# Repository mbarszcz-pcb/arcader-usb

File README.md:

# ArcadeR-USB
A Replacement PCB that brings USB connectivity to the Retroradionics ArcadeR Joystick based on the Daemonbite Arcade Encoder and the Arduino Leonardo.

Quick Links
* [Schematic](pdf/arcader-usb-1.0-schematic.pdf)
* [Gerber Files](gerbers)
* [PCB Renderings](images/pcb)
* [Photos](images/photos)

## Introduction
The ArcadeR USB is an open source PCB project with firmware based on the open source [DaemonBite Arcade Encoder Firmware](https://github.com/MickGyver/DaemonBite-Arcade-Encoder) and circuit design based on the Arduino Leonardo.  The original PCB inside the ArcadeR output provided Atari/Amiga/C64 style outputs through a DB9 connector.  While the DB9 connector is great for retro computers and consoles, using the ArcadeR with a PC, Raspberry Pi, or MiSTER requires external adapters.  Moreover, many of the inexpensive adapters introduced significant input latency, running the experience.

The ArcadeR USB aims to solve these problems plus introduces some extra features by simply providing a new PCB that fits inside the joystick with no modifications require and allows you to simply plug in the internal joystick and button cables.

## Features:
* DIY / Open Source
* Simple installation. Remove the screws, replace the PCB and cable, and plug everything back in
* Built around the Atmega32U4, Arduino Libraries, and DaemonBite Arcade Encoder firmware.  Use the firmware as-is or customize however you see fit
* Functions as a standard HID Gamepad, so no extra drivers required
* Replaces the two front latching switches with tactile switches wired as individually addressable buttons.  Now the front buttons can be used for Start/Select, Coin/Start, pressed together to bring up menus in emulation, or even used as an additional button in games
* Quickly link/unlink the two buttons on the fly with a simple button press.  Unlike with the original PCB, no opening of the case and rewiring of the buttons is required to link the two main buttons.  Simply press and hold the top two buttons for 1 second to link or unlink the buttons.  Now you can quickly switch between left and right handed use for 1 button games, or unlink the buttons and use them independently with arcade games that take advantage of both buttons.  The ArcadeR USB saves your last setting to the EEPROM of the Atmega32U4, so your buttons will stay linked or unlinked even after unplugging the controller.
* Designed with customization and DIY in mind.  With open firmware, Arduino library support, a standard Arduino ICSP header for reprogramming, and 2.54mm pin headers on the board for all button and joystick inputs, you can mix, match, rewrite, and reconfigure the ArcadeR to suit your needs
* Fits ready to use “Zero Delay USB Encoder” USB to JST-XH cables with built in strain relief or any other USB cable soldered directly to the 2.54mm headers.

## Bill of Materials (BOM)
* [Excel BOM](ArcadeR-USB-BOM.xlsx)

| Reference  | Type                   | Value  | Qty | Manufacturer               | Part #             | Digikey Part                | Description                                  | Sub Part      | Sub Digikey      |
|------------|------------------------|--------|-----|----------------------------|--------------------|-----------------------------|----------------------------------------------|---------------|------------------|
| U1         | Microcontroller        |        | 1   | Microchip                  | ATMEGA32U4RC-AU    | ATMEGA32U4RC-AU-ND          | Microcontroller                              | ATMEGA32U4-AU | ATMEGA32U4-AU-ND |
| J5         | Header                 | 2x3    | 1   | Amphenol ICC (FCI)         | 10129381-906002BLF | 10129381-906002BLF-ND       | 2x3 2.54mm Short Pin Header for ICSP         |               |                  |
| J11        | Connector              | 4      | 1   | JST                        | B4B-XH-A(LF)(SN)   | 455-2249-ND                 | JST-XH Header - 4 Contact (USB)              |               |                  |
| J21, J31   | Connector              | 2      | 2   | Molex                      | 0532610271         | WM7620CT-ND                 | Molex Picoblade 53261 - 2 Contact            |               |                  |
| J41        | Connector              | 5      | 1   | Molex                      | 0532610571         | WM7623CT-ND                 | Molex Picoblade 53261 - 5 Contact            |               |                  |
| SW3        | Tactile Switch         |        | 1   | TE Connectivity ALCOSWITCH | 1825910-6          | 450-1650-ND                 | Tactile Switch (Reset)                       |               |                  |
| SW7, SW8   | Tactile Switch         |        | 2   | E-Switch                   | TL1105JAF250Q      | EG1864-ND                   | Tactile Switch, Right Angle, Plunger for Cap |               |                  |
| SW7A, SW8A | Tactile Switch Cap     |        | 2   | E-Switch                   | 1RBLK              | EG1882-ND                   | Cap-Round                                    |               |                  |
| R1, R2     | 1206 Resistor          | 2.2K   | 2   | Stackpole Electronics Inc  | RMCF1206JT2K20     | RMCF1206JT2K20CT-ND         | 2.2K 1206 Resistor 5%                        |               |                  |
| R3, R4     | 1206 Resistor          | 22     | 2   | Stackpole Electronics Inc  | RMCF1206JT22R0     | RMCF1206JT22R0CT-ND         | 22R 1206 Resistor 5%                         |               |                  |
| R5         | 1206 Resistor          | 10K    | 1   | Stackpole Electronics Inc  | RMCF1206JT10K0     | RMCF1206JT10K0CT-ND         | 10K 1206 Resistor 5%                         |               |                  |
| D1, D2     | 1206 LED               | Amber  | 1   | Würth Elektronik           | 732-4988-1-ND      | 732-4988-1-ND               | Amber 1206 LED                               |               |                  |
| C1, C4, C5 | 1206 Ceramic Capacitor | 1uF    | 3   | KEMET                      | C1206C105K4RACTU   | 399-1254-1-ND               | 1uF Ceramic Capacitor 16V                    |               |                  |
| C2, C3     | 1206 Ceramic Capacitor | 22pF   | 2   | KEMET                      | C1206C220K3HAC7800 | 399-C1206C220K3HAC7800CT-ND | 22pF Ceramic Capacitor 25V                   |               |                  |
| C6         | 1206 Ceramic Capacitor | 10uF   | 1   | KEMET                      | C1206C106K4RACTU   | 399-3525-1-ND               | 10uF Ceramic Capacitor 16V                   |               |                  |
| C7         | 1206 Ceramic Capacitor | 0.1uF  | 1   | KEMET                      | C1206C104K4RACTU   | 399-9305-1-ND               | 0.1uF Ceramic Capacitor 16V                  |               |                  |
| Y1         | Crystal                | 16 MHz | 1   | TXC CORPORATION            | AS-16.000MAHK-B    | 887-1591-ND                 | 16 MHz Crystal - 20-22pF                     |               |                  |

* [Recommended "Zero-Delay USB Encoder" cable](https://focusattack.com/spare-4-pin-to-usb-cable-for-zero-delay-usb-encoder-pcb/).  Other USB cables can be used, but you may need to add a JST XH connector or strip the cable and solder the 4 wires directly to the PCB.

## Building the ArcadeR USB
Most of the build is pretty self explanitory, although there are a few things to keep in mind.

* For ease of use, I'd recommend buying can buying the USB cable designed for the Zero-Delay USB encoder.  This cable is inexpensive and comes with the correct JST XH connector already installed along with a strain relief.  You can use any USB cable though and crimp the JST connector on it, or omit the JST connector all together, and solder it directly into the 0.1" throguh holes on the PCB.

* The ICSP pin header is a tight fit in the joystick.  It is designed to be mounted to the bottom of the board, but ensure that you check fitment before soldering the pin header.  Depending on the length of your headers, you may need to "cheat" by pushing the header against a hard surface to make the pin length a bit shorter.  If need be, trim any excess length off the back of the pin header (top of the board) to preserve the bevel on the pin header.

* I recommend installing the front facing right angle tactile switches into the PCB, fitting the PCB into the Arcader USB joystick housing, and then soldering 1 or 2 of the pins on the tactile switches in place.  This will ensure a nice straight fit on the front buttons.

* The reset button has proven to be unnecessary and can simply be omitted in most cases.  I have not needed to use the reset button as the Arduino IDE can auto-reset the microcontroller over USB.  My recommendation would simply be to not include it and if a reset is needed, short the pads with a small pair of tweezers.  Although it can be made to work, it is a tight fit under the right fire button.  If you do decide to include it, care must be taken to ensure the connectors on the bottom of fire button 2 are not depressing the reset button when assembled.  The best way I've found to ensure enough clearance is to unplug the two connectors on the bottom of the fire button, bend the two flat tabs completely flat, and then reattach the connector.

* If you plug your ArcadeR USB into your system and nothing happens, check that the reset button isn't being held down.  

* When you close up the case, take care to make sure nothing is being pinched and the cables aren't interfering with the closing of the case.  The strain relief at the front is a fairly tight fit though.

## Programming the ArcadeR USB
Once the board has been assembled, you will need to program the microcontroller as an Arduino Leonardo and then load the firmware sketch. 

### Part 1 - Burn the Arduino Bootloader
The Atmega32u4 on the ArcadeR USB needs to be programmed as an Arduino Leonardo compatible device so it can be recognized and prorgrammed by the Arduino IDE.  This only has to be done once.  There are two ways to accomplish this:

1.  By using an AVR programmer such as this one from [Sparkfun](https://learn.sparkfun.com/tutorials/installing-an-arduino-bootloader/hardware-hookup)

2.  By using another Arduino (Uno or compatible) in an "Arduino as ISP" configuration.  If you have another Arduino laying around, this will let you program the ArcaderUSB without having to purchase a separate programmer.  This was how I programmed mine.

The ICSP header on the ArcadeR USB is compatible with the standard Arduino ICSP pinout, and can be programmed as per the examples [here](https://www.arduino.cc/en/Tutorial/BuiltInExamples/ArduinoISP#how-to-wire-your-boards).  When programming the microcontroller, it is important not to connect the USB cable to your PC until this has been completed.  Connect up your Arduino Uno to the ICSP header on the ArcaderUSB board, and follow the instructions above.  The key here is to select "Programmer: Arduino as ISP" and "Board:" as Arduino Leonardo.  The "board" setting is the board you are programming INTO the Atmega32u4 (we're making the ArcadeR USB a Leonardo), not the board you are programming it from (Likely an Arduino UNO).

### Part 2 - Load the firmware sketch
Once the ICSP programming is complete, disconnect the ICSP header.  You will need the [Arudino IDE](https://www.arduino.cc/en/software) installed to load the firmware (Arduino sketch) onto the ArcadeR USB.  If you have used an Arduino before, this part should be very familiar.  Connect your USB cable and attach the ArcadeR USB to your computer.  Select File > Open and navigate to the .ino sketch of the firmware.  Under the tools menu, select board: "Arduino Leonardo"

Once everything is set, hit Sketch > Upload.  If the board does not program successfully, check Device manager to make sure the Arduino Leonardo is showing up under "Ports (COM & LPT)".  If not, check your cables and make sure the ICSP completed successfully.  Once the sketch has been uploaded, unplug the Arcader USB from your computer and reconnect it.  If you are on a Windows PC, you can hit start > run > type "joy.cpl" and hit enter.  This will open the Game Controllers configuration, and you should now see a controller named "Arduino Leonardo".  When you hit properties, it will display the buttons and joystick axis.  Move the joystick around and test that all your buttons and directions are working.  If there are any issues, go back and check your soldering and cables.  Any changes to the firmware can simply be done over USB now without the ICSP header or disassembling the joystick.

## Using the ArcadeR USB
* The firmware is designed to use the HID Joystick library, so no additional drivers are required and it should be out-of-the-box compatible with most systems.

* To link/unlink the two fire buttons, simply hold the top two buttons for about 1 second until the LED flashes.  This indicates that the buttons have been linked/unlinked.  This setting is stored in the EEPROM of the Atmega32u4, so it will be restored automatically the next time you use the joystick.

* The firmware sketch can be edited and re-uploaded to the controller if you wish to change the behavior of the joystick.  One tweak you may wish to make is to change DEBOUNCE 0 to DEBOUNCE 1 to enable the debouncing routines if you have debouncing with the buttons.  If you are so inclided, you can also edit the board types in the Arduino configuration directory to reprogram the device ID and name to something more to your liking.

## Links
* [Retro Radionics - Maker of the ArcadeR Joystick](https://retroradionics.co.uk/)
* [Arduino IDE](https://www.arduino.cc/en/software)
* [Daemonbite Arcade Encoder Firmware Project](https://github.com/MickGyver/DaemonBite-Arcade-Encoder)

## License
This PCB design and the firmware are licensed as GNU General Public License v3.0.  The DaemonBite Arcade Encoder firmware was modified with additional functionality specific to the ArcadeR USB PCB in accordance with it's GPL3 license.  For additional details please see [LICENSE](LICENSE)

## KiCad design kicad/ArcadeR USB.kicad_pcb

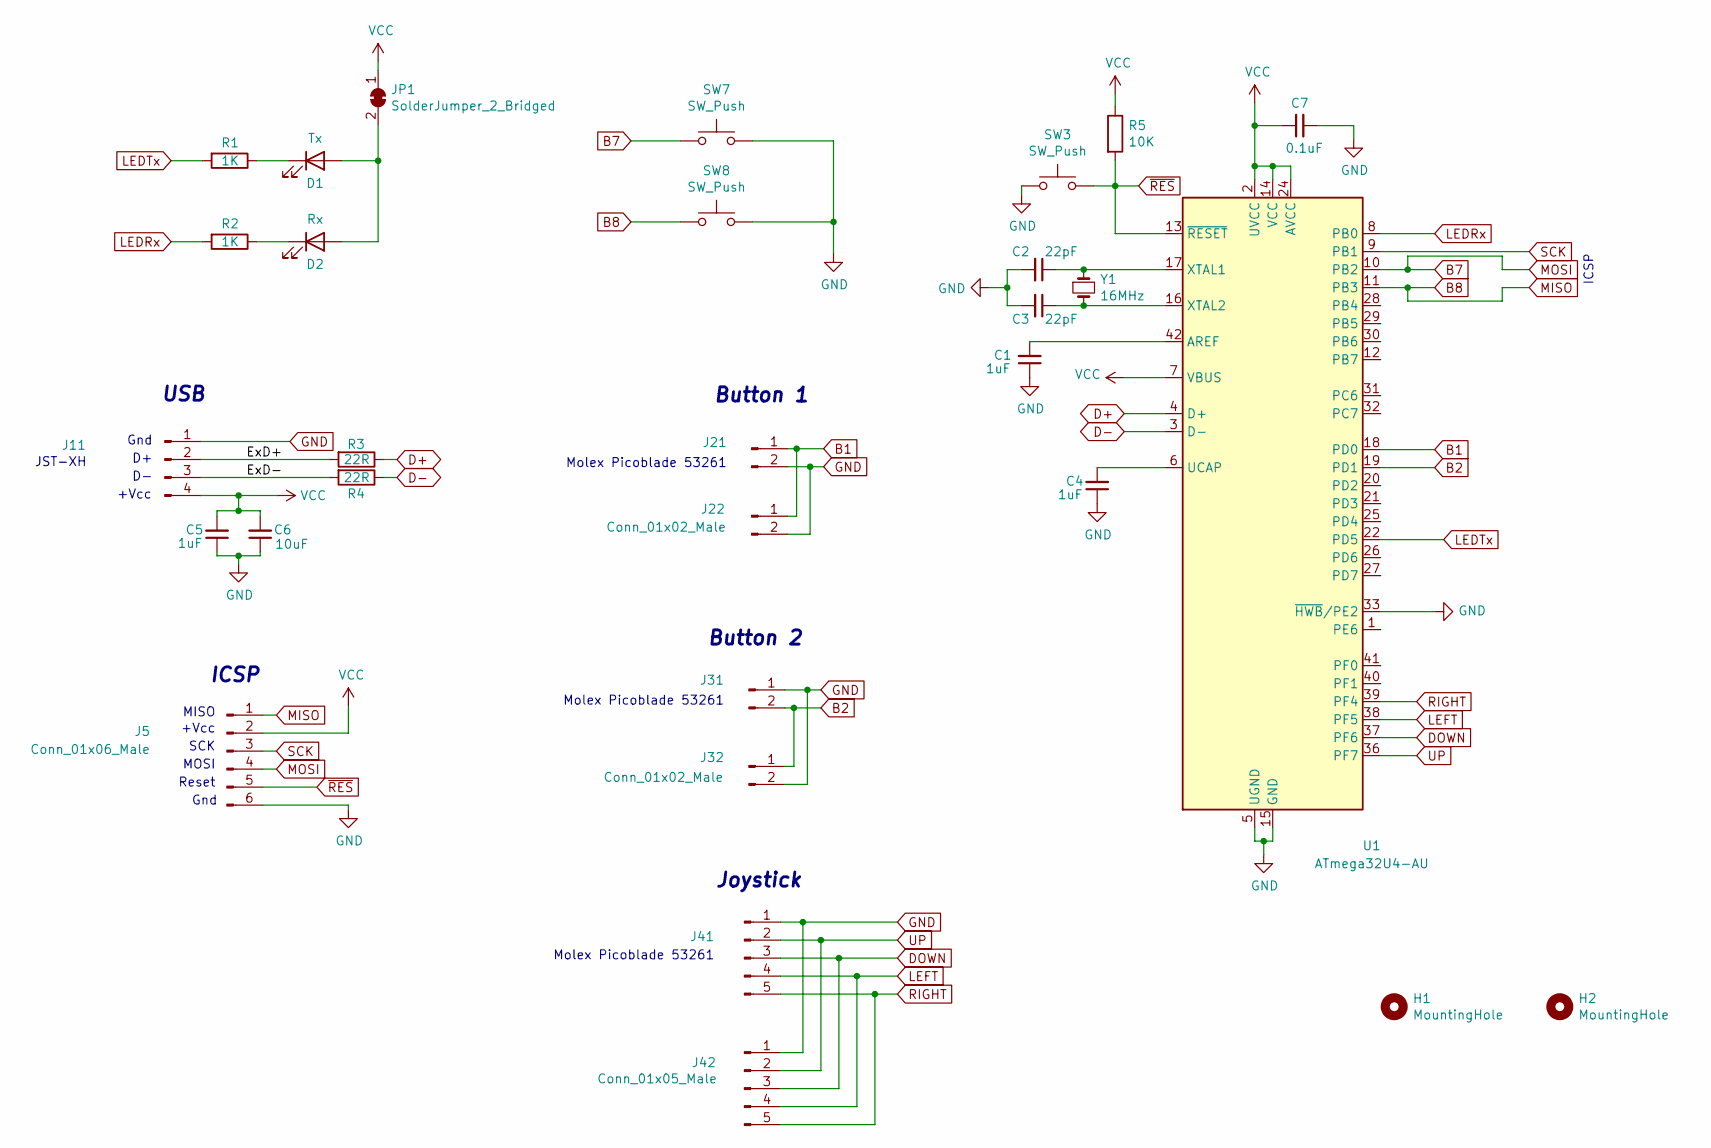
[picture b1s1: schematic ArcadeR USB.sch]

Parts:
C1, C4, C5: 1uF; C_1206_3216Metric_Pad1.42x1.75mm_HandSolder
C2, C3: 22pF; C_1206_3216Metric_Pad1.42x1.75mm_HandSolder
C6: 10uF; C_1206_3216Metric_Pad1.42x1.75mm_HandSolder
C7: 0.1uF; C_1206_3216Metric_Pad1.42x1.75mm_HandSolder
D1: Tx; LED_1206_3216Metric_Pad1.42x1.75mm_HandSolder
D2: Rx; LED_1206_3216Metric_Pad1.42x1.75mm_HandSolder
H1, H2: MountingHole; MountingHole_3.5mm
J5: Conn_01x06_Male; PinHeader_2x03_P2.54mm_Vertical
J11: Conn_01x04_Male; JST_XH_B4B-XH-A_1x04_P2.50mm_Vertical-BoxSilk-Back
J21, J31: Conn_01x02_Male; Molex_PicoBlade_53261-0271_1x02-1MP_P1.25mm_Horizontal
J22, J32: Conn_01x02_Male; PinHeader_1x02_P2.54mm_Vertical-BoxSilk
J41: Conn_01x05_Male; Molex_PicoBlade_53261-0571_1x05-1MP_P1.25mm_Horizontal
J42: Conn_01x05_Male; PinHeader_1x05_P2.54mm_Vertical-BoxSilk
JP1: SolderJumper_2_Bridged; SolderJumper-2_P1.3mm_Bridged_RoundedPad1.0x1.5mm
R1, R2: 1K; R_1206_3216Metric_Pad1.42x1.75mm_HandSolder
R3, R4: 22R; R_1206_3216Metric_Pad1.42x1.75mm_HandSolder
R5: 10K; R_1206_3216Metric_Pad1.42x1.75mm_HandSolder
SW3: SW_Push; SW_PUSH_6mm_H4.3mm
SW7, SW8: SW_Push; SW_Tactile_SPST_Angled_PTS645Vx83-2LFS-DoubleSidedSS
U1: ATmega32U4-AU; TQFP-44_10x10mm_P0.8mm
Y1: 16MHz; Crystal_HC49-4H_Vertical

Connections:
/ExD+: J11.2, R3.2
/ExD-: J11.3, R4.2
B1: J21.1, J22.1, U1.18 (PD0)
B2: J31.2, J32.1, U1.19 (PD1)
B7: J5.4, SW7.1, U1.10 (PB2)
B8: J5.1, SW8.2, U1.11 (PB3)
D+: R3.1, U1.4 (D+)
D-: R4.1, U1.3 (D-)
DOWN: J41.3, J42.3, U1.37 (PF6)
GND: C1.1, C2.2, C3.2, C4.1, C5.1, C6.1, C7.2, J5.6, J11.1, J21.2, J22.2, J31.1, J32.2, J41.1, J42.1, SW3.2, SW7.2, SW8.1, U1.5 (UGND), U1.15 (GND), U1.23 (GND), U1.33 (~HWB~/PE2), U1.35 (GND), U1.43 (GND)
LEDRx: R2.2, U1.8 (PB0)
LEDTx: R1.2, U1.22 (PD5)
LEFT: J41.4, J42.4, U1.38 (PF5)
unnamed: C1.2, U1.42 (AREF)
unnamed: C2.1, U1.17 (XTAL1), Y1.1
unnamed: C3.1, U1.16 (XTAL2), Y1.2
unnamed: C4.2, U1.6 (UCAP)
unnamed: D1.1 (K), R1.1
unnamed: D1.2 (A), D2.2 (A), JP1.2 (B)
unnamed: D2.1 (K), R2.1
RIGHT: J41.5, J42.5, U1.39 (PF4)
SCK: J5.3, U1.9 (PB1)
UP: J41.2, J42.2, U1.36 (PF7)
VCC: C5.2, C6.2, C7.1, J5.2, J11.4, JP1.1 (A), R5.1, U1.2 (UVCC), U1.7 (VBUS), U1.14 (VCC), U1.24 (AVCC), U1.34 (VCC), U1.44 (AVCC)
~RES: J5.5, R5.2, SW3.1, U1.13 (~RESET)

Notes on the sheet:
Button 1
Button 2
Joystick
Molex Picoblade 53261
ICSP
MISO
+Vcc
SCK
MOSI
Reset
Gnd
JST-XH
USB

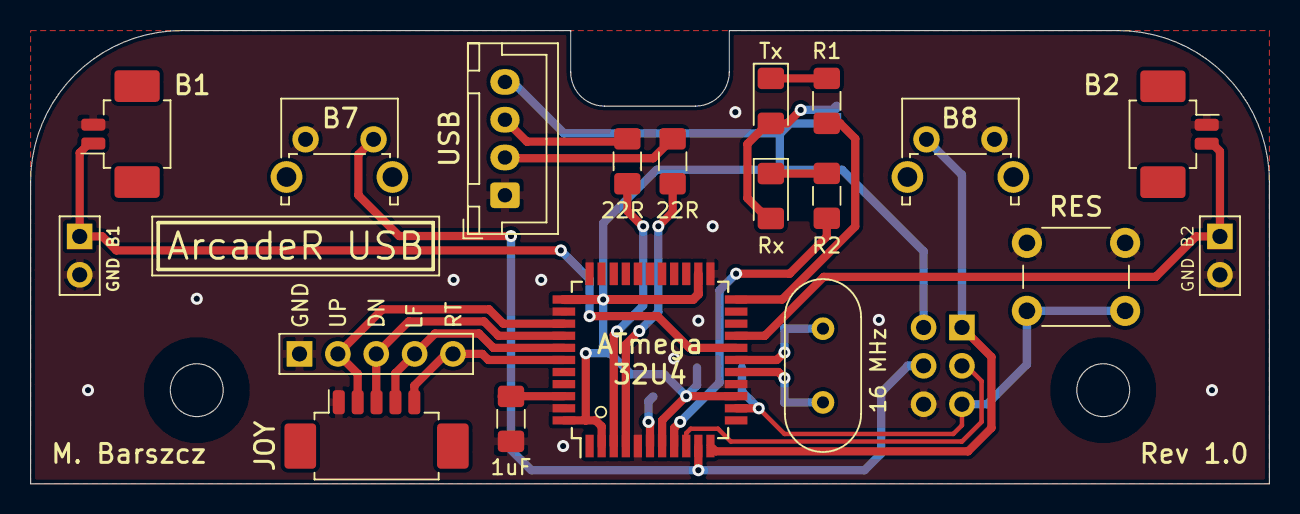
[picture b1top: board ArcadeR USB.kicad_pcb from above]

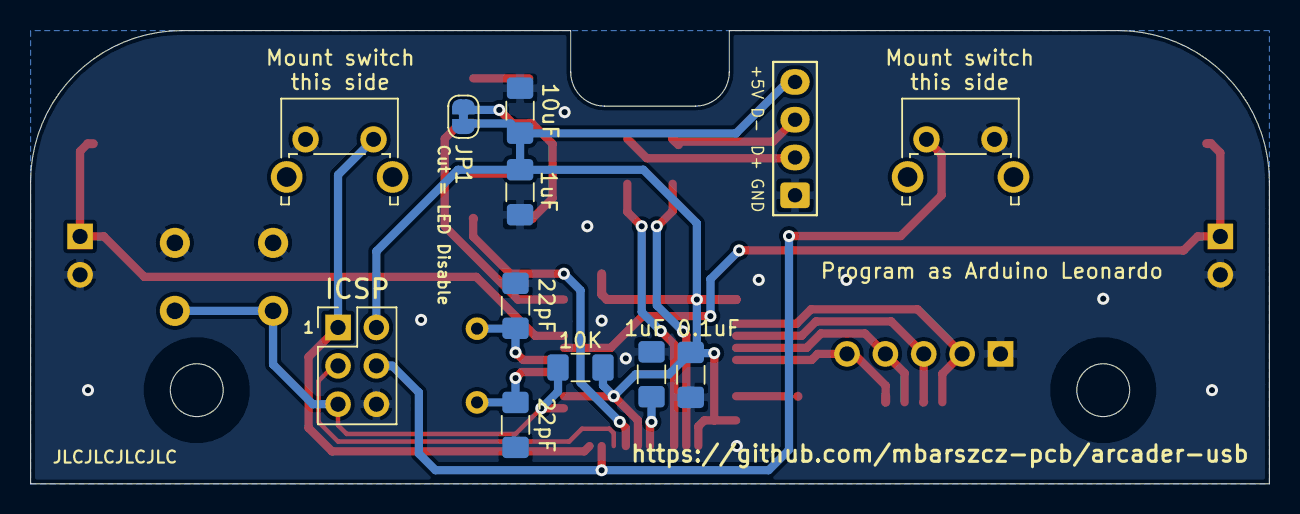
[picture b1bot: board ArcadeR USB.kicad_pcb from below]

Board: 2 copper layers, 82.0 x 30.0 mm, 30 parts (11 on the bottom side), 25 nets.

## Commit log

2021-06-06 Initial upload
2021-06-06 updated photos
2021-06-06 fixed bom file name
2021-06-06 added photos
2021-12-09 Update DaemonBiteArcadeEncoderArcadeR-1.0.ino
    Fixed missing * in comments.
